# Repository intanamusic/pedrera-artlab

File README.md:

Overview
========

When music and space blend together.
The music of the band INTANA and the innovation from Fab Lab Barcelona / Institut d’Arquitectura Avançada de Catalunya (IAAC) join together to present a unique and experimental concert.

A live performance where space and the interpretation of sounds and lights will be one together, where technology and design will create an interactive atmosphere that will accompany and dialogue with the melodies and rhythms of the quartet formed by Núria Moliner, Guillem Callejón, Jordi Mestres and Ricard Parera.

The project, led by Marc Conangla (designer) and Núria Moliner (architect and composer), will be developed by a multidisciplinary team coordinated by Santi Fuentemilla (architect) and Esteban Giménez (engineer and programmer) with Fab Lab Barcelona (IAAC) as the main collaborator, and staged on April 26 in the auditorium of La Pedrera, Barcelona. 

Process
=======

Coding
------

Flatdoc is a small JavaScript file that fetches Markdown files and renders them
as full pages. Essentially, it's the easiest
way to make open source documentation from *Readme* files.

``` javascript
Flatdoc.run({
  fetcher: Flatdoc.github('USER/REPO')
});
```

Prototypes
----------

Misc
====

Inspirations
-------------

The following projects have inspired Flatdoc.

 * [Backbone.js] - Jeremy's projects have always adopted this "one page
 documentation" approach which I really love.

 * [Docco] - Jeremy's Docco introduced me to the world of literate programming,
 and side-by-side documentation in general.

 * [Stripe] - Flatdoc took inspiration on the look of their API documentation.

 * [DocumentUp] - This service has the same idea but does a hosted readme 
 parsing approach.

[rsc]: http://ricostacruz.com
[c]:   http://github.com/rstacruz/flatdoc/contributors

[GitHub API]: http://github.com/api
[marked]: https://github.com/chjj/marked
[Backbone.js]: http://backbonejs.org
[dox]: https://github.com/visionmedia/dox
[Stripe]: https://stripe.com/docs/api
[Docco]: http://jashkenas.github.com/docco
[GitHub pages]: https://pages.github.com
[fences]:https://help.github.com/articles/github-flavored-markdown#syntax-highlighting
[DocumentUp]: http://documentup.com

[project]: https://github.com/rstacruz/flatdoc
[template]: https://github.com/rstacruz/flatdoc/raw/gh-pages/templates/template.html
[blank]: https://github.com/rstacruz/flatdoc/raw/gh-pages/templates/blank.html
[dist]: https://github.com/rstacruz/flatdoc/tree/gh-pages/v/0.9.0

Attributions
-------------

**Intana**

Web: http://intanamusic.com/

Facebook: https://www.facebook.com/intanamusic

Twitter: https://twitter.com/intana_music

Instagram: https://www.instagram.com/intana_music/

Spotify: https://open.spotify.com/artist/1MJy23jZGgB8MH8h2lLz0u

Núria Moliner, Guillem Callejón, Jordi Mestres i Ricard Parera

**FablabBCN**

Web: https://fablabbcn.org/

Facebook: https://www.facebook.com/FabLab.BCN/

Twitter: https://twitter.com/fablabbcn

Instagram: https://www.instagram.com/fablabbcn/

Marc Conangla: http://archive.fabacademy.org/archives/2017/fablabbcn/students/421/

Esteban Giménez: http://archive.fabacademy.org/archives/2017/fablabbcn/students/271/

Santi Fuentemilla:
https://iaac.net/people/santi-fuentemilla/

**IAAC** 

Web: https://iaac.net/

Facebook: https://www.facebook.com/IAACbcn/

Twitter: https://twitter.com/iaac

Instagram: https://www.instagram.com/iaacbcn/

**Pedrera-Artlab**

Flatdoc offers a few harmless, unobtrusive extras that come in handy in building
documentation sites.

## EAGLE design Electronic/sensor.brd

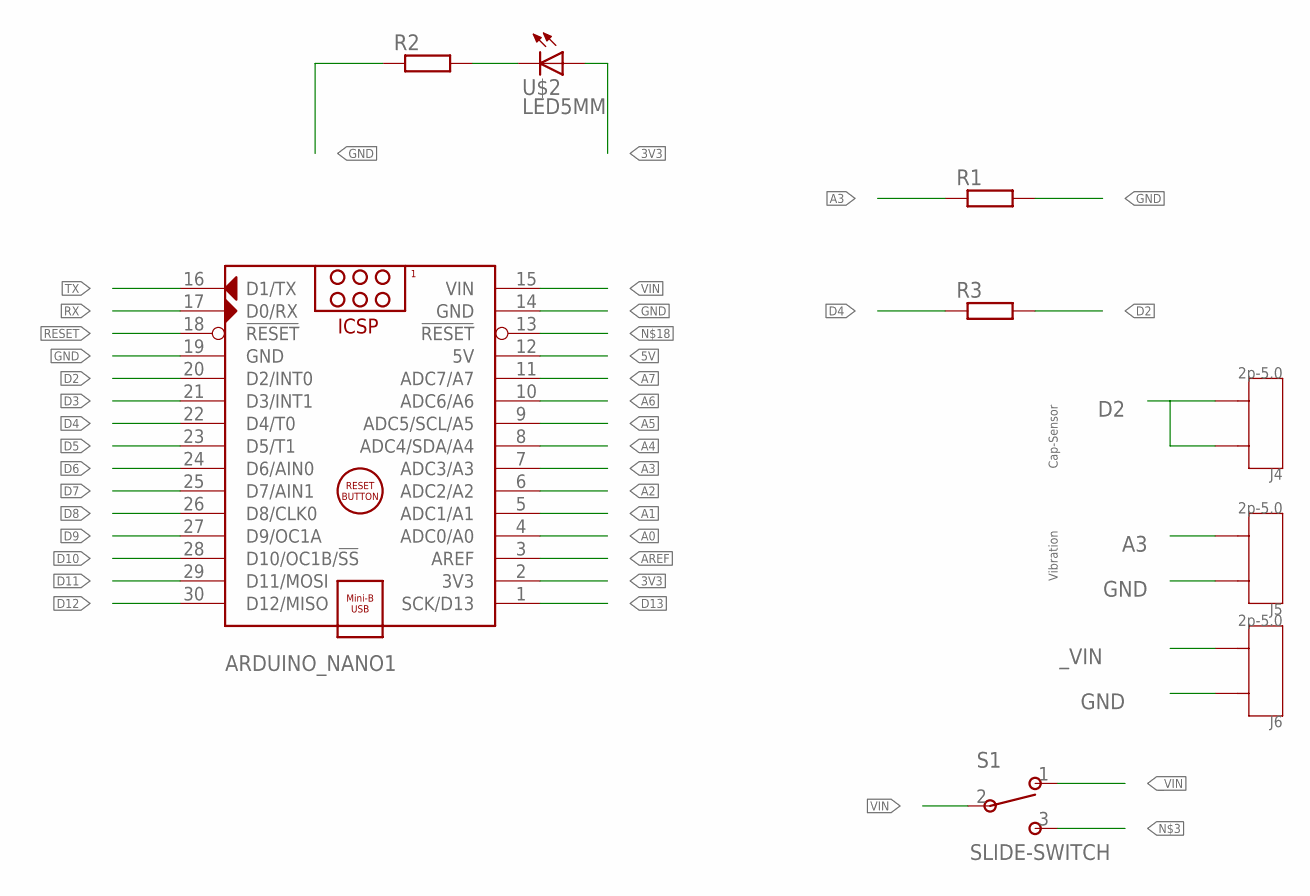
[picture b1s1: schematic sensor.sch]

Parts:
ARDUINO_NANO1: ARDUINO_NANO
J4, J5, J6: 2p-5.0; H2-5.0
R1, R2, R3: R0204/7; 0204/7
S1: SLIDE-SWITCH; AYZ0102AGRLC
U$2: LED5MM; 5MM

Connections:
3V3: ARDUINO_NANO1.2 (3V3), U$2.IN (A)
5V: ARDUINO_NANO1.12 (5V)
A0: ARDUINO_NANO1.4 (ADC0/A0)
A1: ARDUINO_NANO1.5 (ADC1/A1)
A2: ARDUINO_NANO1.6 (ADC2/A2)
A3: ARDUINO_NANO1.7 (ADC3/A3), J5.2, R1.1
A4: ARDUINO_NANO1.8 (ADC4/SDA/A4)
A5: ARDUINO_NANO1.9 (ADC5/SCL/A5)
A6: ARDUINO_NANO1.10 (ADC6/A6)
A7: ARDUINO_NANO1.11 (ADC7/A7)
AREF: ARDUINO_NANO1.3 (AREF)
D2: ARDUINO_NANO1.20 (D2/INT0), J4.1, J4.2, R3.2
D3: ARDUINO_NANO1.21 (D3/INT1)
D4: ARDUINO_NANO1.22 (D4/T0), R3.1
D5: ARDUINO_NANO1.23 (D5/T1)
D6: ARDUINO_NANO1.24 (D6/AIN0)
D7: ARDUINO_NANO1.25 (D7/AIN1)
D8: ARDUINO_NANO1.26 (D8/CLK0)
D9: ARDUINO_NANO1.27 (D9/OC1A)
D10: ARDUINO_NANO1.28 (D10/OC1B/!SS)
D11: ARDUINO_NANO1.29 (D11/MOSI)
D12: ARDUINO_NANO1.30 (D12/MISO)
D13: ARDUINO_NANO1.1 (SCK/D13)
GND: ARDUINO_NANO1.14 (GND), ARDUINO_NANO1.19 (GND), J5.1, J6.1, R1.2, R2.1
unnamed: R2.2, U$2.OUT (C)
RESET: ARDUINO_NANO1.18 (!RESET)
RX: ARDUINO_NANO1.17 (D0/RX)
TX: ARDUINO_NANO1.16 (D1/TX)
VIN: ARDUINO_NANO1.15 (VIN), S1.2
_VIN: J6.2, S1.1

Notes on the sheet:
Cap-Sensor
Vibration

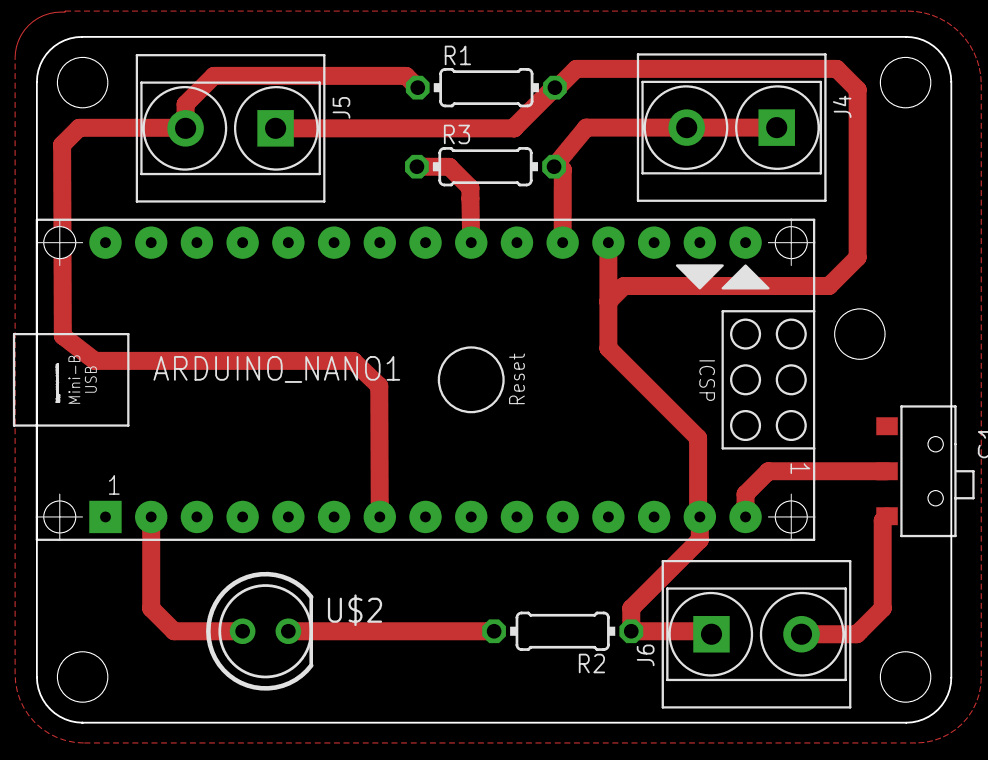
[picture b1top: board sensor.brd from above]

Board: 2 copper layers, 50.8 x 38.1 mm, 9 parts (0 on the bottom side), 8 nets.

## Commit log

2018-01-16 docs
2018-01-16 actualització
2018-01-16 actu
2018-01-16 actua
2018-01-16 index
2018-02-24 hackthelightup
2018-04-18 arduino codigo
2018-04-18 actu arduino
2018-04-19 arduino files
2018-04-19 scripts
2018-04-20 scripts python
2018-04-20 pages
